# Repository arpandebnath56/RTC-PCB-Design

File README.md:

# RTC-PCB-Design

A KiCad-based Real-Time Clock (RTC) Module PCB design project featuring circuit schematics, PCB layout, 3D visualization, and footprint integration.

## Project Contents

- Circuit Schematic
- PCB Layout and Routing
- 3D PCB Visualization
- Footprint Resources
- KiCad Project Files

## Tools Used

- KiCad EDA
- Electronic Circuit Design
- PCB Layout Design
- 3D PCB Visualization

## Author

Arpan Debnath  
B.Tech in Electronics and Communication Engineering

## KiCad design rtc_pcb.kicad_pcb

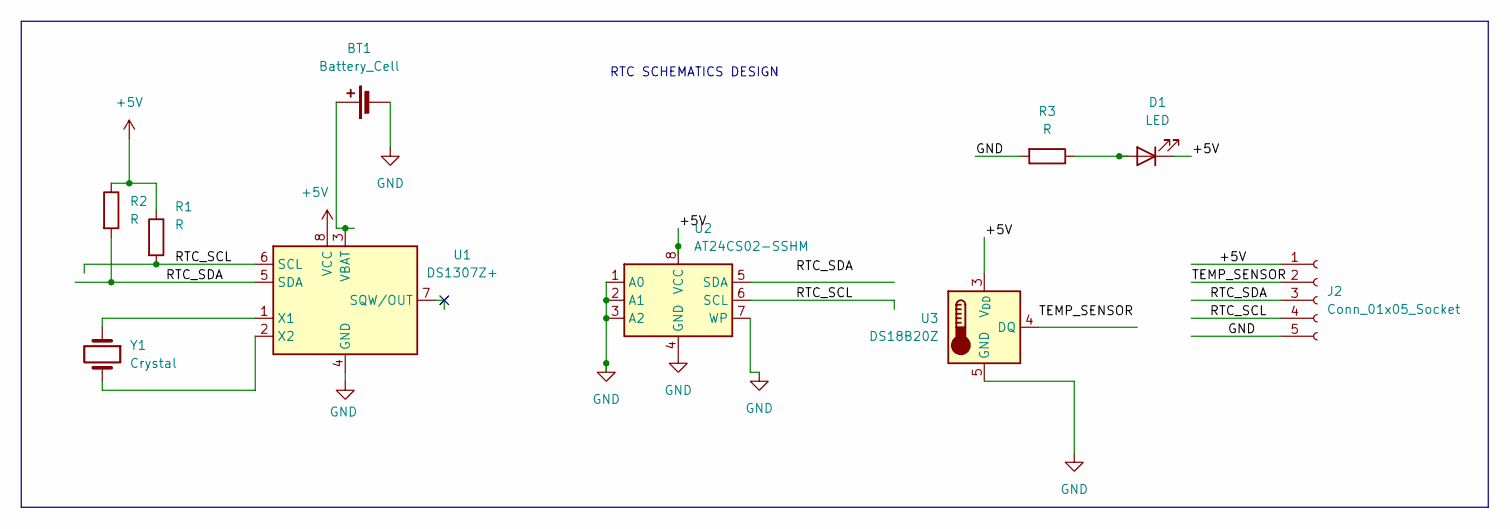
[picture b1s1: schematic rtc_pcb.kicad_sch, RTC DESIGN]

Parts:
BT1: Battery_Cell; SOT-23-6
D1: LED; LED_Cree-XHP50_3V_HighDensity
J2: Conn_01x05_Socket; PinHeader_1x05_P2.54mm_Vertical
R1, R2, R3: R; R_0402_1005Metric
U1: DS1307Z+; SOIC-8_3.9x4.9mm_P1.27mm
U2: AT24CS02-SSHM; SOIC-8_3.9x4.9mm_P1.27mm
U3: DS18B20Z; SOIC-8_3.9x4.9mm_P1.27mm
Y1: Crystal; SOIC-8_3.9x4.9mm_P1.27mm

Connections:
+5V: D1.1 (K), J2.1, R1.1, R2.1, U1.8 (VCC), U2.8 (VCC), U3.3 (V_{DD})
/RTC_SCL: J2.4, R1.2, U1.6 (SCL), U2.6 (SCL)
/RTC_SDA: J2.3, R2.2, U1.5 (SDA)
/TEMP_SENSOR: J2.2
GND: BT1.2 (-), J2.5, R3.2, U1.4 (GND), U2.1 (A0), U2.2 (A1), U2.3 (A2), U2.4 (GND), U2.7 (WP), U3.5 (GND)
unnamed: BT1.1 (+), U1.3 (VBAT)
unnamed: D1.2 (A), R3.1
unnamed: U1.1 (X1), Y1.1
unnamed: U1.2 (X2), Y1.2

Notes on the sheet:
RTC SCHEMATICS DESIGN

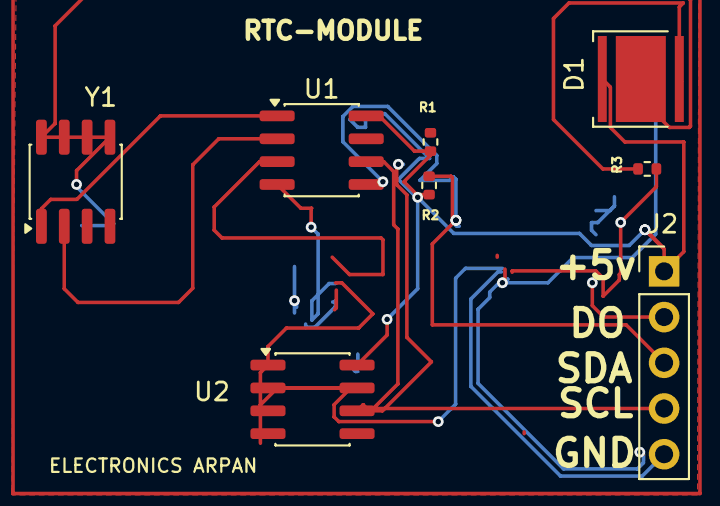
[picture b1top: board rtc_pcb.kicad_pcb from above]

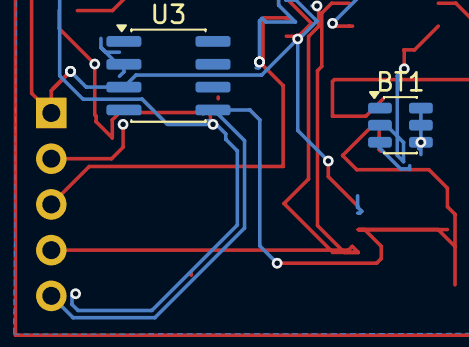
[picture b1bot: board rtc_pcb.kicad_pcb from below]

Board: 2 copper layers, 10 parts (2 on the bottom side), 8 nets.
